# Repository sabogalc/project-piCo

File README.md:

# project piCo

This repository contains KiCad project files for reverse-engineered Raspberry Pi Pico boards, including both the standard RP2040 Pico H and the WiFi version, the Pico WH. There is also a preliminary design for an RP2350 Pico 2 board. The primary goal of this project is two-fold:

1. USB-C Upgrade: Although all Pico boards were released in or after 2021, they all use Micro-USB. The initial aim was to update these boards to include USB-C, making them more compatible with modern standards.

2. Accessibility of Design Files: During this process, I discovered that the original board designs are created in Cadence Allegro, a format that is less accessible due to its encrypted file structure and the expensive software required. This project not only adds USB-C support but also aims to make the design files as free and open as possible.

For detailed information on each board’s design, please refer to their specific folders within the `KiCad Projects` directory. Boardview files for all boards, including the original Pico H, are provided to allow for easy troubleshooting. The designs in this repository are freely available for use without any license restrictions or attribution requirements.

> The USB-C version of the Pico H board.

> The USB-C version of the Pico WH board.

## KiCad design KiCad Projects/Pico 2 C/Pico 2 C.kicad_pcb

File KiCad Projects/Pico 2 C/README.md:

# project piCo 2

I was extremely excited to see the announcement of the Pico 2 last week, but some of my enthusiasm left me when I saw that the new board still retained the Micro-USB connector. Of course, I got right to work on correcting this issue.

### Design Sources

Despite the online documentation and datasheet linking to design files for the board, the link appears to be broken as of August 14, 2024. (See [this issue](https://github.com/raspberrypi/documentation/issues/3809) for more information)

Still, I worked with the schematic and pictures of the board to be able to create an initial version of a Type-C Pico 2.

- **Schematic:** [Raspberry Pi Pico 2 Datasheet](https://datasheets.raspberrypi.com/pico/pico-2-datasheet.pdf#page=23)
- **PCB Pictures (Front & Back):** [Pico 2 PCB Photos](https://blog.zonepi.cz/rapsberry-pi-pico-2/)

Thankfully, with all the work I've already done on reversing the Pico, making this board was a breeze as I was able to reuse many of my assets and resources from the previous boards.

### Design Process

Kicad allows for Reference Images to be placed while routing a board (found in `Place > Add Reference Image`), so I put the aforementioned scans into the project to scale, and based my routing on the photo. This means that my board is not fully 1:1 with the factory one, but in lieu of the official design files, this was the best that could be done right now. An example of this layout is shown below.

### Component Substitutions (IMPORTANT)

As-is, this board is not ready for production. I was unable to figure out what component or footprint L2 is, other than that it is a coupled inductor and measures roughly 1.75x2.2mm. As a stand-in, I have placed an 0602 SMD inductor, but please note that this is **_not correct_**. As before, the boot select switch and 12MHz crystals are compatible substitutes (even though they told us what crystal was used this time, I just reused the asset I already had from the previous design).

### PDF Schematic

A PDF copy of the schematic is available [here](https://github.com/sabogalc/project-piCo/blob/main/KiCad%20Projects/Pico%202%20C/Pico%202%20C.pdf).

### Board Photos

Because of the aforementioned inductor issue, the only photos of this board right now are the KiCad renders. If anybody figures out what inductor this is, please either let me know or make a correction in the form of a pull request.

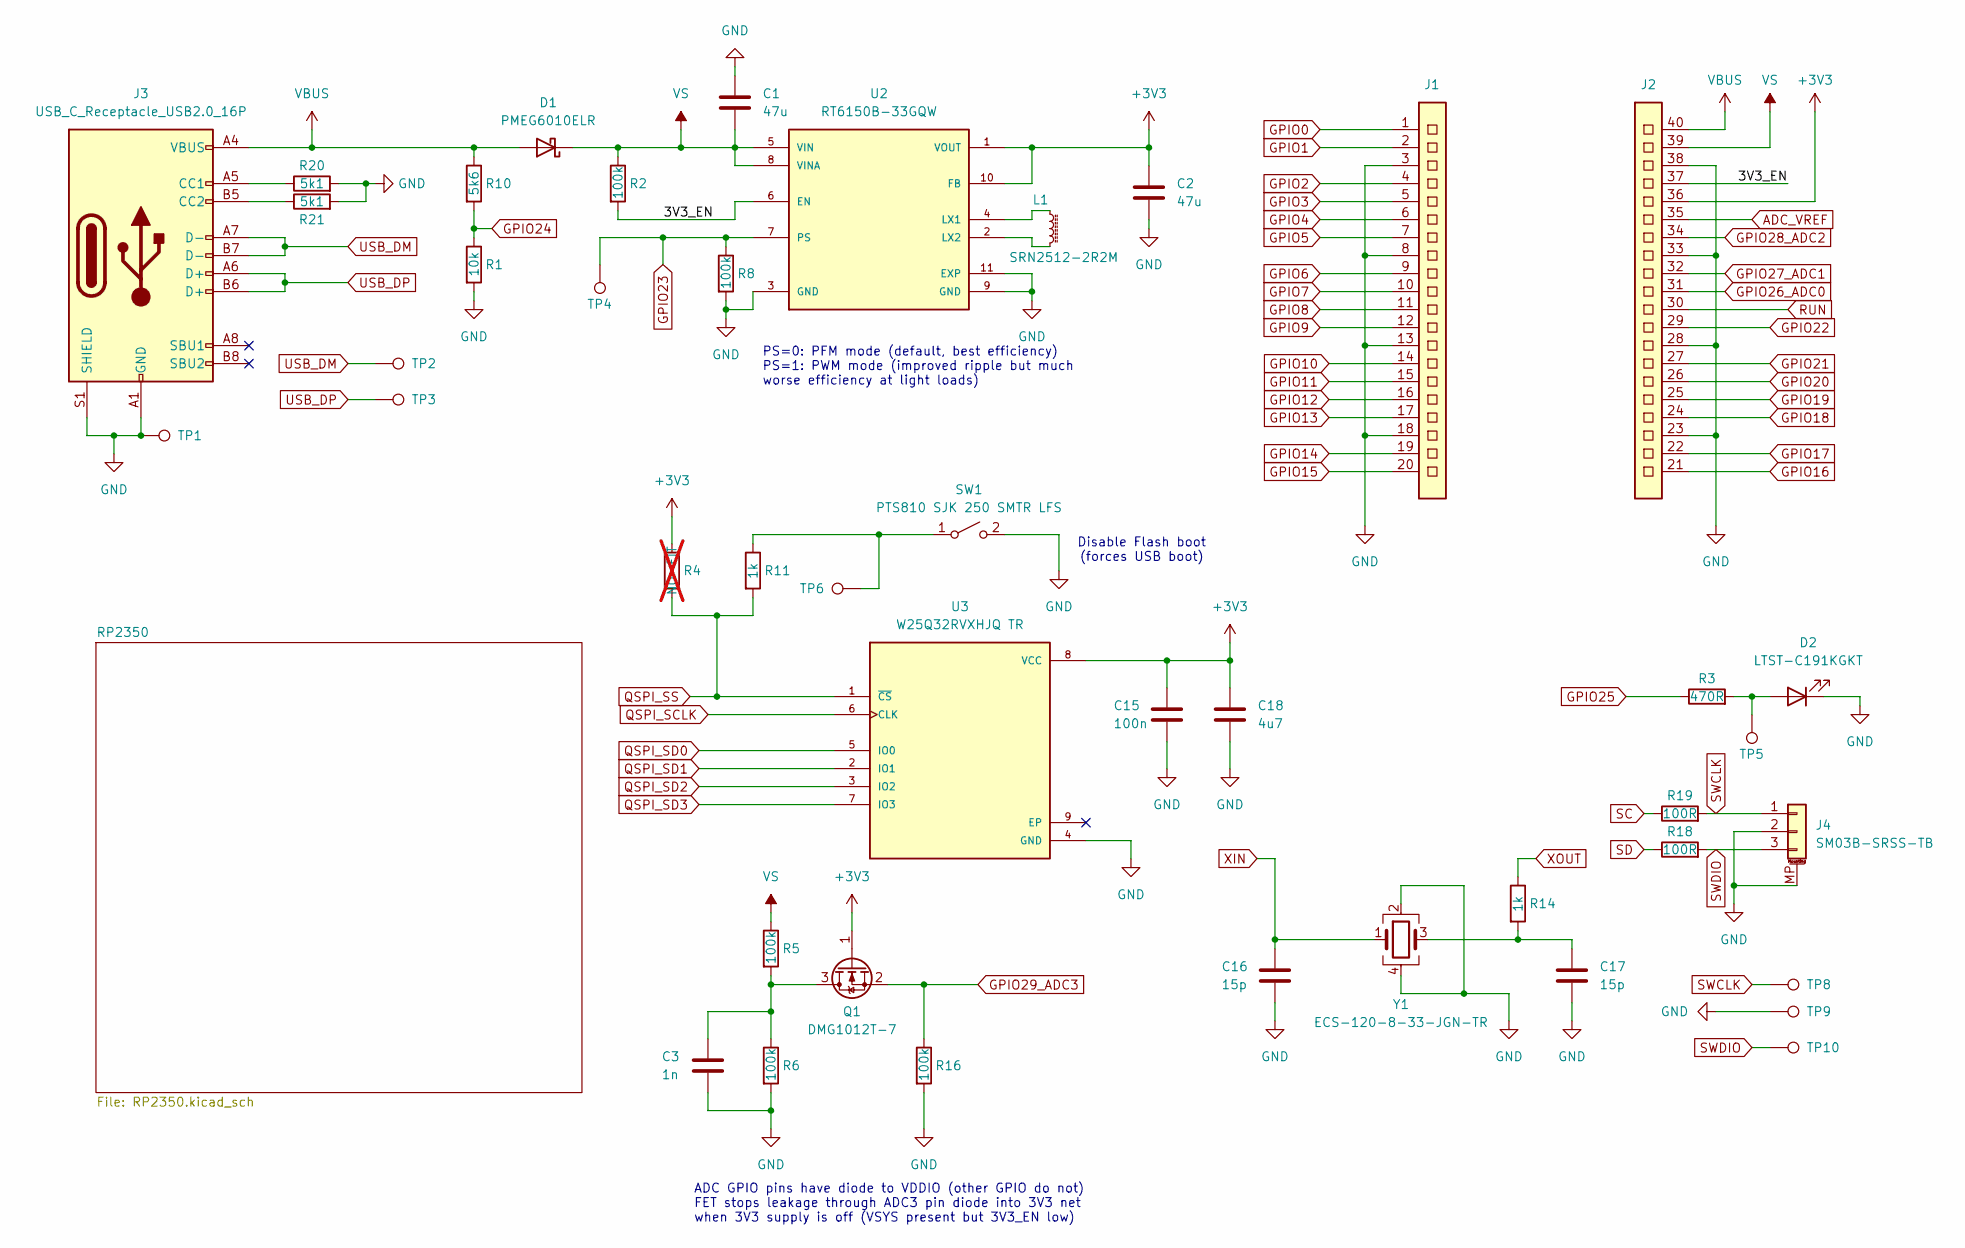
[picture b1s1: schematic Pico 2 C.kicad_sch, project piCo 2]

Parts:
C1, C2: 47u; C_0805_2012Metric
C3: 1n; C_0201_0603Metric
C15: 100n; C_0201_0603Metric
C16, C17: 15p; C_0201_0603Metric
C18: 4u7; C_0402_1005Metric
D1: PMEG6010ELR; D_SOD-123F
D2: LTST-C191KGKT; LED_0603_1608Metric
J1: CON_PICO_1-20
J2: CON_PICO_21-40
J3: USB_C_Receptacle_USB2.0_16P; USB_C_Receptacle_GCT_USB4105-xx-A_16P_TopMnt_Horizontal
J4: SM03B-SRSS-TB; JST_SH_SM03B-SRSS-TB_1x03-1MP_P1.00mm_Horizontal
L1: SRN2512-2R2M; L_1008_2520Metric
Q1: DMG1012T-7; SOT-523
R1: 10k; R_0201_0603Metric
R2, R5, R6, R8, R16: 100k; R_0201_0603Metric
R3: 470R; R_0201_0603Metric
R4: NO-FIT; R_0201_0603Metric; not fitted
R10: 5k6; R_0201_0603Metric
R11, R14: 1k; R_0201_0603Metric
R18, R19: 100R; R_0201_0603Metric
R20, R21: 5k1; R_0402_1005Metric
SW1: PTS810 SJK 250 SMTR LFS; SW_SPST_PTS810
TP1, TP2, TP3, TP4, TP5, TP6, TP8, TP9, TP10: TestPoint; TestPoint_Pad_1.5x1.5mm
U2: RT6150B-33GQW; DFN-10-1EP_2.6x2.6mm_P0.5mm_EP1.3x2.2mm
U3: W25Q32RVXHJQ TR; TDFN-8-1EP_3x2mm_P0.5mm_EP1.3x1.4mm
Y1: ECS-120-8-33-JGN-TR; Crystal_SMD_SeikoEpson_FA238-4Pin_3.2x2.5mm

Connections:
+3V3: C2.1, C15.1, C18.1, J2.36, Q1.1 (G), R4.1, U2.1 (VOUT), U2.10 (FB), U3.8 (VCC); also elsewhere on the board
/3V3_EN: J2.37, R2.2, U2.6 (EN)
ADC_VREF: J2.35; also elsewhere on the board
GND: C1.2, C2.2, C3.2, C15.2, C16.2, C17.2, C18.2, D2.1 (K), J1.3, J1.8, J1.13, J1.18, J2.23, J2.28, J2.33, J2.38, J3.A1 (GND), J3.A12 (GND), J3.B1 (GND), J3.B12 (GND), J3.S1 (SHIELD), J4.2, J4.MP (MountPin), R1.2, R6.2, R8.2, R16.2, R20.2, R21.2, SW1.2 (B), TP1.1, TP9.1, U2.3 (GND), U2.9 (GND), U2.11 (EXP), U3.4 (GND), Y1.2, Y1.4; also elsewhere on the board
GPIO0: J1.1; also elsewhere on the board
GPIO1: J1.2; also elsewhere on the board
GPIO2: J1.4; also elsewhere on the board
GPIO3: J1.5; also elsewhere on the board
GPIO4: J1.6; also elsewhere on the board
GPIO5: J1.7; also elsewhere on the board
GPIO6: J1.9; also elsewhere on the board
GPIO7: J1.10; also elsewhere on the board
GPIO8: J1.11; also elsewhere on the board
GPIO9: J1.12; also elsewhere on the board
GPIO10: J1.14; also elsewhere on the board
GPIO11: J1.15; also elsewhere on the board
GPIO12: J1.16; also elsewhere on the board
GPIO13: J1.17; also elsewhere on the board
GPIO14: J1.19; also elsewhere on the board
GPIO15: J1.20; also elsewhere on the board
GPIO16: J2.21; also elsewhere on the board
GPIO17: J2.22; also elsewhere on the board
GPIO18: J2.24; also elsewhere on the board
GPIO19: J2.25; also elsewhere on the board
GPIO20: J2.26; also elsewhere on the board
GPIO21: J2.27; also elsewhere on the board
GPIO22: J2.29; also elsewhere on the board
GPIO23: R8.1, TP4.1, U2.7 (PS); also elsewhere on the board
GPIO24: R1.1, R10.2; also elsewhere on the board
GPIO25: R3.1; also elsewhere on the board
GPIO26_ADC0: J2.31; also elsewhere on the board
GPIO27_ADC1: J2.32; also elsewhere on the board
GPIO28_ADC2: J2.34; also elsewhere on the board
GPIO29_ADC3: Q1.2 (S), R16.1; also elsewhere on the board
unnamed: C17.1, R14.2, Y1.3
unnamed: D2.2 (A), R3.2, TP5.1
unnamed: J3.A5 (CC1), R20.1
unnamed: J3.B5 (CC2), R21.1
unnamed: C3.1, Q1.3 (D), R5.2, R6.1
unnamed: R11.1, SW1.1 (A), TP6.1
unnamed: L1.1, U2.4 (LX1)
unnamed: L1.2, U2.2 (LX2)
QSPI_SCLK: U3.6 (CLK); also elsewhere on the board
QSPI_SD0: U3.5 (IO0); also elsewhere on the board
QSPI_SD1: U3.2 (IO1); also elsewhere on the board
QSPI_SD2: U3.3 (IO2); also elsewhere on the board
QSPI_SD3: U3.7 (IO3); also elsewhere on the board
QSPI_SS: R4.2, R11.2, U3.1 (~CS); also elsewhere on the board
RUN: J2.30; also elsewhere on the board
SC: R19.1; also elsewhere on the board
SD: R18.1; also elsewhere on the board
SWCLK: J4.1, R19.2, TP8.1
SWDIO: J4.3, R18.2, TP10.1
USB_DM: J3.A7 (D-), J3.B7 (D-), TP2.1; also elsewhere on the board
USB_DP: J3.A6 (D+), J3.B6 (D+), TP3.1; also elsewhere on the board
VBUS: D1.2 (A), J2.40, J3.A4 (VBUS), J3.A9 (VBUS), J3.B4 (VBUS), J3.B9 (VBUS), R10.1
VS: C1.1, D1.1 (K), J2.39, R2.1, R5.1, U2.5 (VIN), U2.8 (VINA)
XIN: C16.1, Y1.1; also elsewhere on the board
XOUT: R14.1; also elsewhere on the board

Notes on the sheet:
ADC GPIO pins have diode to VDDIO (other GPIO do not) FET stops leakage through ADC3 pin diode into 3V3 net when 3V3 supply is off (VSYS present but 3V3_EN low)
Disable Flash boot (forces USB boot)
PS=0: PFM mode (default, best efficiency) PS=1: PWM mode (improved ripple but much worse efficiency at light loads)

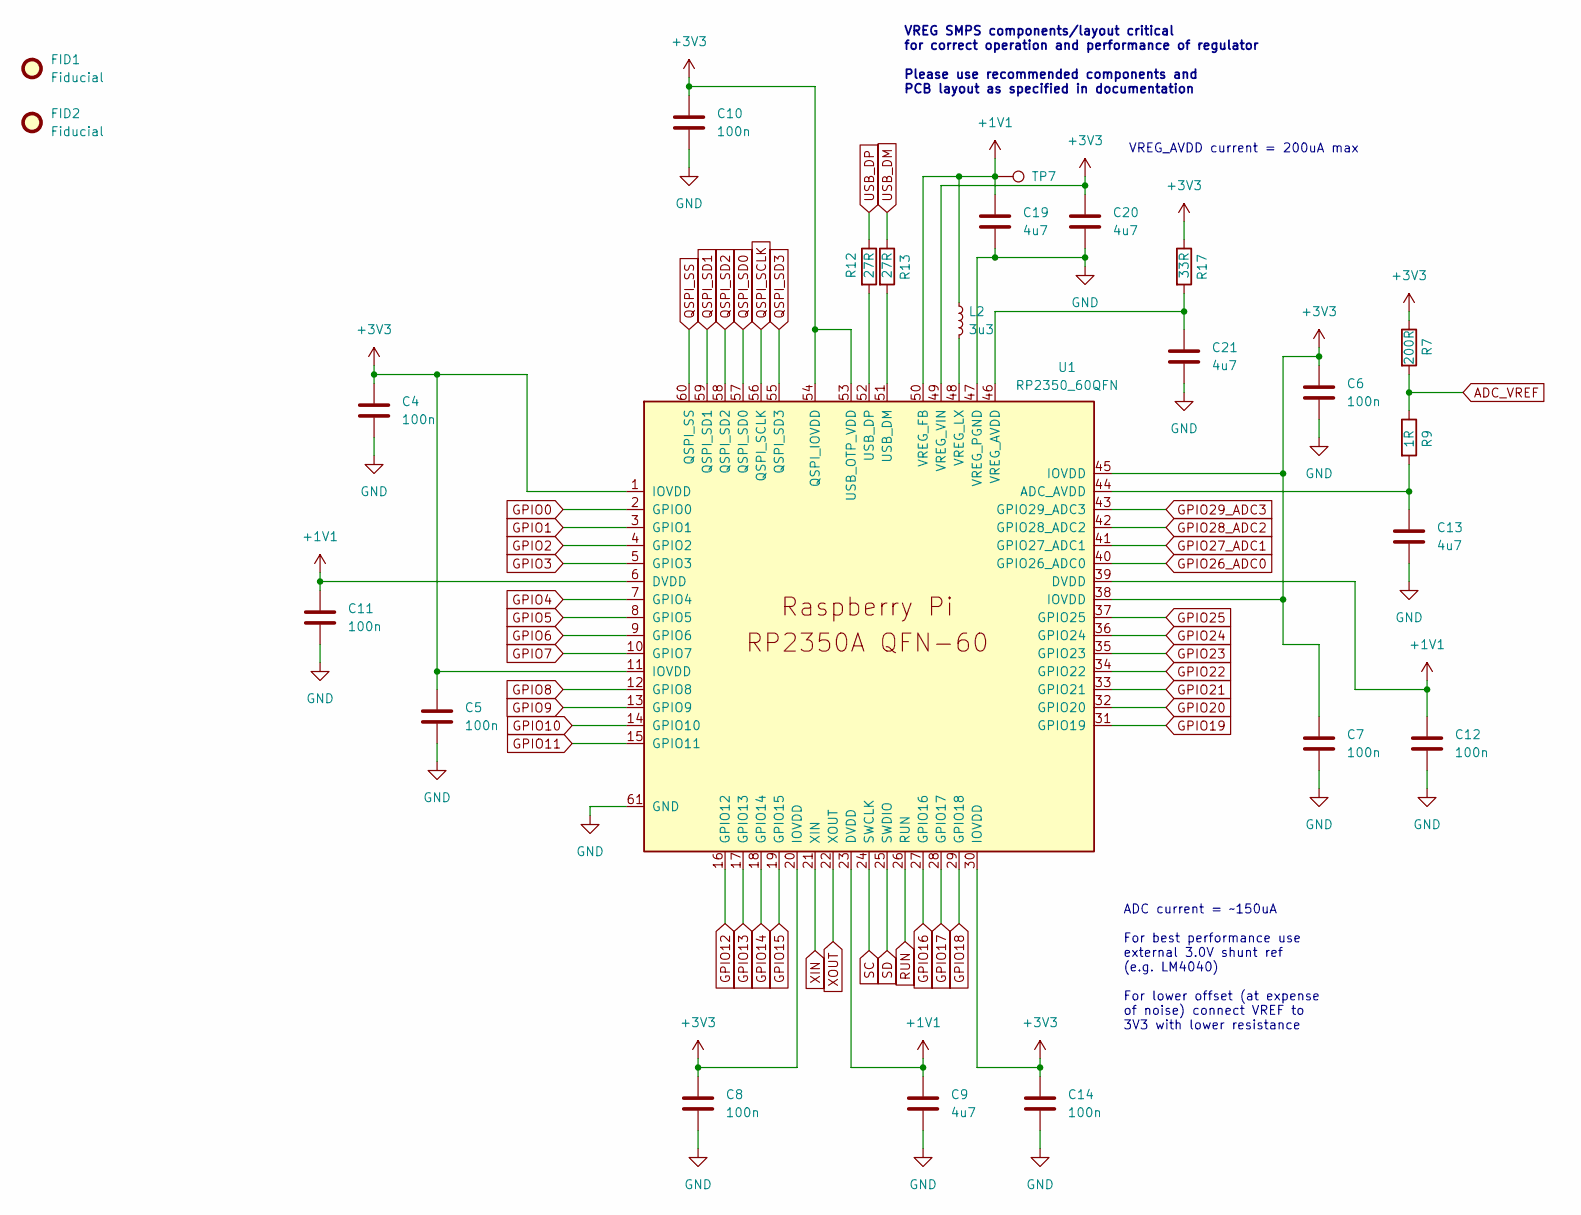
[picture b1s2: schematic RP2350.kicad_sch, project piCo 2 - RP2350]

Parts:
C4, C5, C6, C7, C8, C10, C11, C12, C14: 100n; C_0201_0603Metric
C9: 4u7; C_0201_0603Metric
C13, C19, C20, C21: 4u7; C_0402_1005Metric
FID1, FID2: Fiducial; Fiducial_1mm_Mask2mm
L2: 3u3; AOTA-B201610S3R3-101-T
R7: 200R; R_0402_1005Metric
R9: 1R; R_0201_0603Metric
R12, R13: 27R; R_0201_0603Metric
R17: 33R; R_0402_1005Metric
TP7: TestPoint; TestPoint_Pad_1.5x1.5mm
U1: RP2350_60QFN; RP2350-QFN-60-1EP_7x7_P0.4mm_EP3.4x3.4mm_ThermalVias

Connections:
+1V1: C9.1, C11.1, C12.1, C19.1, L2.1, TP7.1, U1.6 (DVDD), U1.23 (DVDD), U1.39 (DVDD), U1.50 (VREG_FB)
+3V3: C4.1, C5.1, C6.1, C7.1, C8.1, C10.1, C14.1, C20.1, R7.1, R17.1, U1.1 (IOVDD), U1.11 (IOVDD), U1.20 (IOVDD), U1.30 (IOVDD), U1.38 (IOVDD), U1.45 (IOVDD), U1.49 (VREG_VIN), U1.53 (USB_OTP_VDD), U1.54 (QSPI_IOVDD); also elsewhere on the board
ADC_VREF: R7.2, R9.1; also elsewhere on the board
GND: C4.2, C5.2, C6.2, C7.2, C8.2, C9.2, C10.2, C11.2, C12.2, C13.2, C14.2, C19.2, C20.2, C21.2, U1.47 (VREG_PGND), U1.61 (GND); also elsewhere on the board
GPIO0: U1.2 (GPIO0); also elsewhere on the board
GPIO1: U1.3 (GPIO1); also elsewhere on the board
GPIO2: U1.4 (GPIO2); also elsewhere on the board
GPIO3: U1.5 (GPIO3); also elsewhere on the board
GPIO4: U1.7 (GPIO4); also elsewhere on the board
GPIO5: U1.8 (GPIO5); also elsewhere on the board
GPIO6: U1.9 (GPIO6); also elsewhere on the board
GPIO7: U1.10 (GPIO7); also elsewhere on the board
GPIO8: U1.12 (GPIO8); also elsewhere on the board
GPIO9: U1.13 (GPIO9); also elsewhere on the board
GPIO10: U1.14 (GPIO10); also elsewhere on the board
GPIO11: U1.15 (GPIO11); also elsewhere on the board
GPIO12: U1.16 (GPIO12); also elsewhere on the board
GPIO13: U1.17 (GPIO13); also elsewhere on the board
GPIO14: U1.18 (GPIO14); also elsewhere on the board
GPIO15: U1.19 (GPIO15); also elsewhere on the board
GPIO16: U1.27 (GPIO16); also elsewhere on the board
GPIO17: U1.28 (GPIO17); also elsewhere on the board
GPIO18: U1.29 (GPIO18); also elsewhere on the board
GPIO19: U1.31 (GPIO19); also elsewhere on the board
GPIO20: U1.32 (GPIO20); also elsewhere on the board
GPIO21: U1.33 (GPIO21); also elsewhere on the board
GPIO22: U1.34 (GPIO22); also elsewhere on the board
GPIO23: U1.35 (GPIO23); also elsewhere on the board
GPIO24: U1.36 (GPIO24); also elsewhere on the board
GPIO25: U1.37 (GPIO25); also elsewhere on the board
GPIO26_ADC0: U1.40 (GPIO26_ADC0); also elsewhere on the board
GPIO27_ADC1: U1.41 (GPIO27_ADC1); also elsewhere on the board
GPIO28_ADC2: U1.42 (GPIO28_ADC2); also elsewhere on the board
GPIO29_ADC3: U1.43 (GPIO29_ADC3); also elsewhere on the board
unnamed: C13.1, R9.2, U1.44 (ADC_AVDD)
unnamed: R13.2, U1.51 (USB_DM)
unnamed: R12.2, U1.52 (USB_DP)
unnamed: C21.1, R17.2, U1.46 (VREG_AVDD)
unnamed: L2.2, U1.48 (VREG_LX)
QSPI_SCLK: U1.56 (QSPI_SCLK); also elsewhere on the board
QSPI_SD0: U1.57 (QSPI_SD0); also elsewhere on the board
QSPI_SD1: U1.59 (QSPI_SD1); also elsewhere on the board
QSPI_SD2: U1.58 (QSPI_SD2); also elsewhere on the board
QSPI_SD3: U1.55 (QSPI_SD3); also elsewhere on the board
QSPI_SS: U1.60 (QSPI_SS); also elsewhere on the board
RUN: U1.26 (RUN); also elsewhere on the board
SC: U1.24 (SWCLK); also elsewhere on the board
SD: U1.25 (SWDIO); also elsewhere on the board
USB_DM: R13.1; also elsewhere on the board
USB_DP: R12.1; also elsewhere on the board
XIN: U1.21 (XIN); also elsewhere on the board
XOUT: U1.22 (XOUT); also elsewhere on the board

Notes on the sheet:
VREG SMPS components/layout critical for correct operation and performance of regulator Please use recommended components and PCB layout as specified in documentation
ADC current = ~150uA For best performance use external 3.0V shunt ref (e.g. LM4040) For lower offset (at expense of noise) connect VREF to 3V3 with lower resistance
VREG_AVDD current = 200uA max

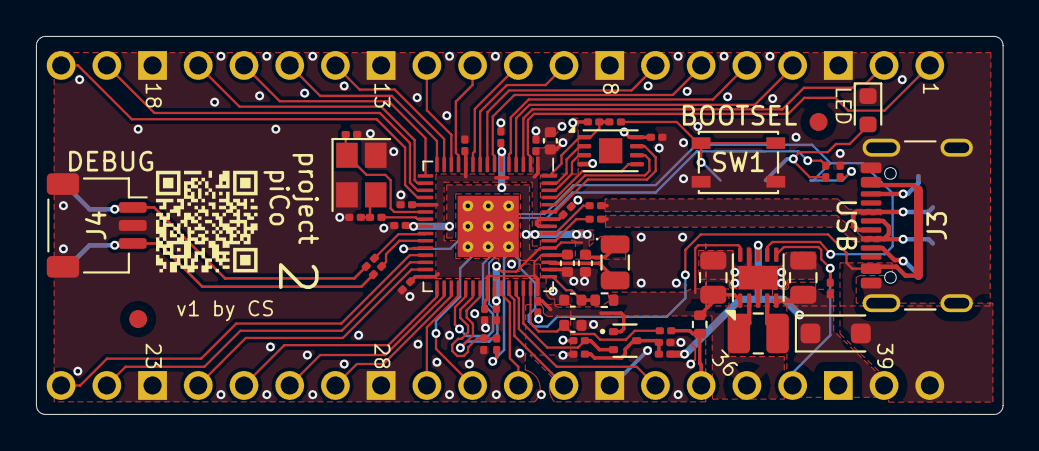
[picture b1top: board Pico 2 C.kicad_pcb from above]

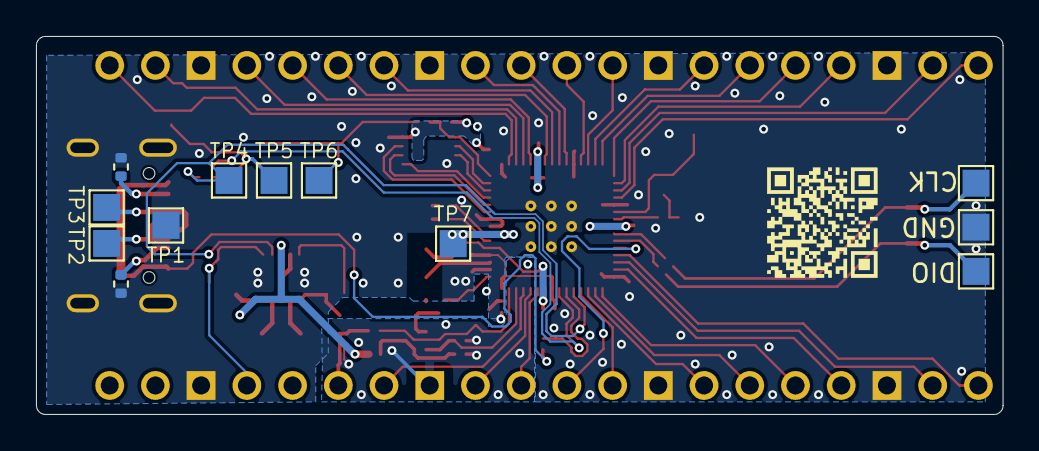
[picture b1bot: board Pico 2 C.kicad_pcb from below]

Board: 2 copper layers, 53.7 x 21.0 mm, 67 parts (12 on the bottom side), 65 nets.

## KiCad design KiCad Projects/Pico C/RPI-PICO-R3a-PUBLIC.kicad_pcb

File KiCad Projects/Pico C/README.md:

# project piCo

This is a completely reverse-engineered Raspberry Pi Pico H made in KiCad version 8. The Raspberry Pi Foundation offers schematics and board layout files for the original board, but they are made in Cadence Allegro, which costs a crisp $1,500/month that I do not have. Instead, I opted to recreate the board in KiCad so that I could add a Type-C port.

### Overview

Initially, I developed a PCB to convert the original Micro-USB signals to a Type-C breakout board. However, the tolerances were really tight, and it didn't look like much of a finished product. My boss gave me a suggestion to redesign the entire board and add a Type-C port to it, which is what I ended up doing. I started the process with the original design files, which you can find in the section below.

### Design Sources

- **Schematic:** [Raspberry Pi Pico Datasheet](https://datasheets.raspberrypi.com/pico/pico-datasheet.pdf#page=26)
- **PCB Design Files:** [RPi Pico R3 Files](https://datasheets.raspberrypi.com/pico/RPi-Pico-R3-PUBLIC-20200119.zip) (Note: This link will download files directly.)
- **BOM:** [Pico Bill of Materials](https://archive.is/NHUY5)

The mechanical layout provided by the Pi Foundation was extremely useful in creating my board dimensions. Since my footprint was made in KiCad, anybody should be able to implement it for their own projects.

### Footprint Differences

The project includes a footprint named "CON_PICO_40W," which replicates the original footprint, and a modified version, "CON_PICO_40W_VER_C," which is used in my design. Key differences are highlighted below.

### Design Evolution

Version 1 of the board had many issues. You can see that version [here](https://github.com/sabogalc/project-piCo/tree/4ffbc08c13815f0195cdc85224667cf2c5e13563). The biggest challenge was fitting the Type-C port within the original dimensions.

When I published this project, many people let me know that Type-C Pico clones already exist, so I modeled my redesign after the purple clone board from [this AliExpress listing](https://www.aliexpress.com/item/3256805444428998.html).

The revised design removed the 4 mounting holes and added space for the Type-C port, which vastly improved my ability to design and route this board. The "CON_PICO_40W_VER_C" footprint used in this revision is a copy of the purple clone board. Sometimes you just need to [reverse-engineer the reverse-engineers](https://youtu.be/FVEQJNRmfDQ?t=431).

### Component Substitutions

I could not find the original boot select switch, Schottky diode, or 12MHz crystal in stock anywhere, but the substitutions I made should be plug-and-play.

### PDF Schematic

For those of you without KiCad or that just want to take a quick look at the schematic, a [PDF version](https://github.com/sabogalc/project-piCo/blob/main/KiCad%20Projects/Pico%20C/RPI-PICO-R3a-PUBLIC.pdf) is available.

### Version 4 - A 1:1 recreation

[Version 3](https://github.com/sabogalc/project-piCo/tree/0116e01858a51d29eb83f16cde15d637a825e509) of this board improved on [version 2](https://github.com/sabogalc/project-piCo/tree/e2333728981e60bb3f34c05a658cf739d1d45163) in regards to copper pours, routing, and silkscreen labeling. However, versions 1-3 were all routed from scratch by myself. As seen below in the `Official Files` section or in the [piCo W folder](https://github.com/sabogalc/project-piCo/tree/main/KiCad%20Projects/Pico%20WH%20-%20No%20License), I later learned how to convert a Cadence Allegro board into a KiCad one, and this allows me to make a 1:1 PCB when reverse-engineering. Version 4 is this 1:1 render, and it should theoretically be the last version of this board.

When it comes to improving the Pico, I have thought about making design improvements to the ADC or adding a reset switch. However, the overall purpose of this project is to be 1:1 with the layout and parts of an original Pico, though if anyone finds any room for improvement I would be happy to make any fixes (e.g. the grid on the schematic is not standard and could use correction).

_**DISCLAIMER**_

I have interned at this company for almost two years.

For those of you that want a board with the aforementioned improvements, check out the [RP2040 board from Out of the Box](https://www.ootbelec.com/store/p/ootb-rp2040).

### Official Files

I have updated this folder to include a file called `RPI-PICO-R3a-PUBLIC - Official.kicad_pcb`. This is as close to the original Cadence Allegro design file that I could get imported into KiCad. I first converted the Allegro board into an Altium one, and then I converted the Altium board into KiCad.

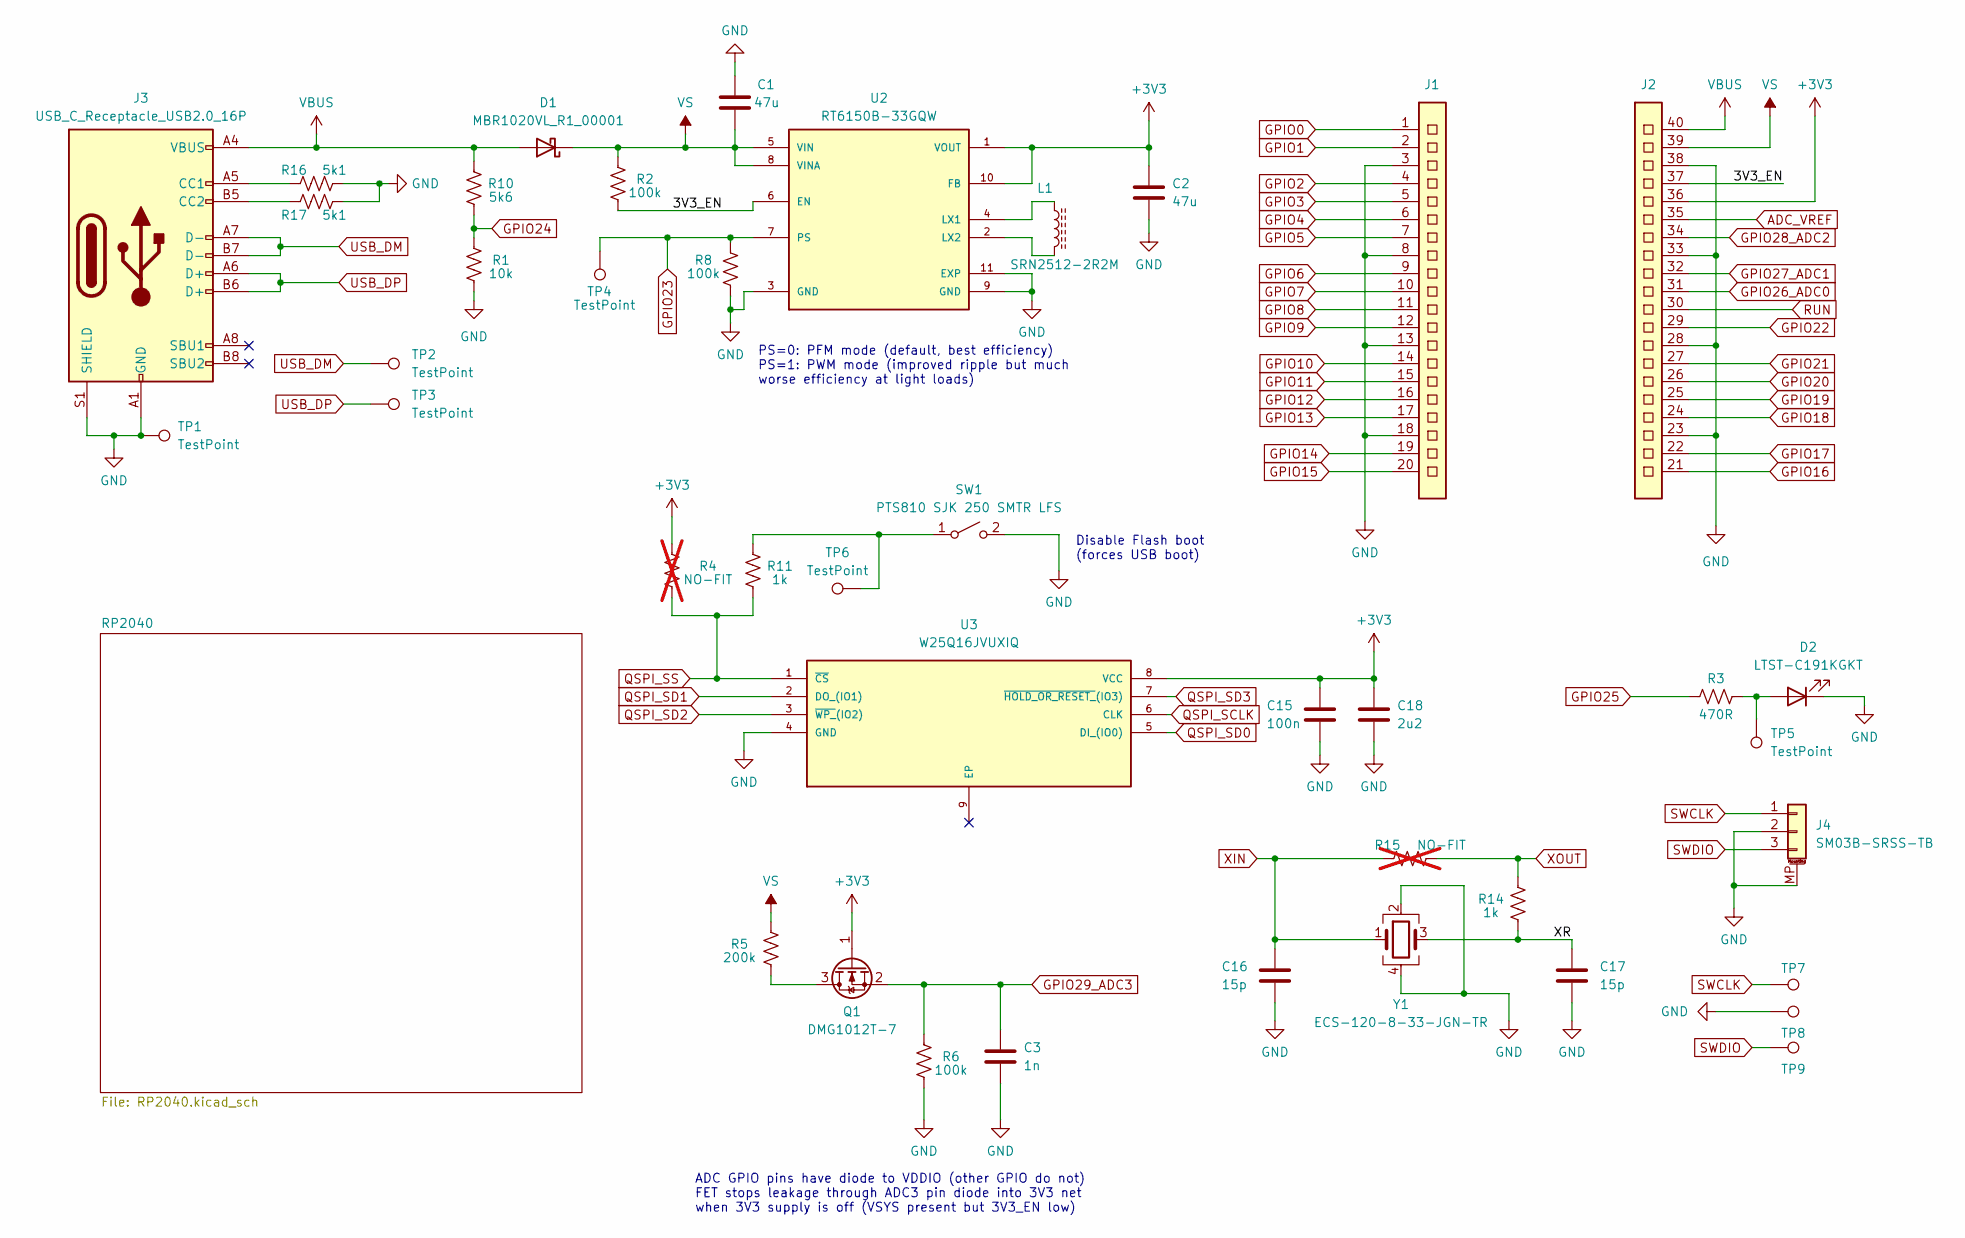
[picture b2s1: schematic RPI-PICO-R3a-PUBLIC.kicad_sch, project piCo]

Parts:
C1, C2: 47u; C_0805_2012Metric
C3: 1n; C_0201_0603Metric
C15: 100n; C_0201_0603Metric
C16, C17: 15p; C_0201_0603Metric
C18: 2u2; C_0402_1005Metric
D1: MBR1020VL_R1_00001; D_SOD-123F
D2: LTST-C191KGKT; LED_0603_1608Metric
J1: CON_PICO_1-20
J2: CON_PICO_21-40
J3: USB_C_Receptacle_USB2.0_16P; USB_C_Receptacle_GCT_USB4105-xx-A_16P_TopMnt_Horizontal
J4: SM03B-SRSS-TB; JST_SH_SM03B-SRSS-TB_1x03-1MP_P1.00mm_Horizontal
L1: SRN2512-2R2M; L_1008_2520Metric
Q1: DMG1012T-7; SOT-523
R1: 10k; R_0402_1005Metric
R2, R6, R8: 100k; R_0402_1005Metric
R3: 470R; R_0402_1005Metric
R4, R15: NO-FIT; R_0402_1005Metric; not fitted
R5: 200k; R_0402_1005Metric
R10: 5k6; R_0402_1005Metric
R11, R14: 1k; R_0402_1005Metric
R16, R17: 5k1; R_0402_1005Metric
SW1: PTS810 SJK 250 SMTR LFS; SW_SPST_PTS810
TP1, TP2, TP3, TP4, TP5, TP6, TP7, TP8, TP9: TestPoint; TestPoint_Pad_1.5x1.5mm
U2: RT6150B-33GQW; DFN-10-1EP_2.6x2.6mm_P0.5mm_EP1.3x2.2mm
U3: W25Q16JVUXIQ; SON50P300X200X60-9N
Y1: ECS-120-8-33-JGN-TR; Crystal_SMD_SeikoEpson_FA238-4Pin_3.2x2.5mm

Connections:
+3V3: C2.1, C15.1, C18.1, J2.36, Q1.1 (G), R4.2, U2.1 (VOUT), U2.10 (FB), U3.8 (VCC); also elsewhere on the board
/3V3_EN: J2.37, R2.1, U2.6 (EN)
/XR: C17.1, R14.1, Y1.3
ADC_VREF: J2.35; also elsewhere on the board
GND: C1.2, C2.2, C3.2, C15.2, C16.2, C17.2, C18.2, D2.1 (K), J1.3, J1.8, J1.13, J1.18, J2.23, J2.28, J2.33, J2.38, J3.A1 (GND), J3.A12 (GND), J3.B1 (GND), J3.B12 (GND), J3.S1 (SHIELD), J4.2, J4.MP (MountPin), R1.1, R6.1, R8.2, R16.2, R17.2, SW1.2 (B), TP1.1, TP8.1, U2.3 (GND), U2.9 (GND), U2.11 (EXP), U3.4 (GND), Y1.2, Y1.4; also elsewhere on the board
GPIO0: J1.1; also elsewhere on the board
GPIO1: J1.2; also elsewhere on the board
GPIO2: J1.4; also elsewhere on the board
GPIO3: J1.5; also elsewhere on the board
GPIO4: J1.6; also elsewhere on the board
GPIO5: J1.7; also elsewhere on the board
GPIO6: J1.9; also elsewhere on the board
GPIO7: J1.10; also elsewhere on the board
GPIO8: J1.11; also elsewhere on the board
GPIO9: J1.12; also elsewhere on the board
GPIO10: J1.14; also elsewhere on the board
GPIO11: J1.15; also elsewhere on the board
GPIO12: J1.16; also elsewhere on the board
GPIO13: J1.17; also elsewhere on the board
GPIO14: J1.19; also elsewhere on the board
GPIO15: J1.20; also elsewhere on the board
GPIO16: J2.21; also elsewhere on the board
GPIO17: J2.22; also elsewhere on the board
GPIO18: J2.24; also elsewhere on the board
GPIO19: J2.25; also elsewhere on the board
GPIO20: J2.26; also elsewhere on the board
GPIO21: J2.27; also elsewhere on the board
GPIO22: J2.29; also elsewhere on the board
GPIO23: R8.1, TP4.1, U2.7 (PS); also elsewhere on the board
GPIO24: R1.2, R10.1; also elsewhere on the board
GPIO25: R3.1; also elsewhere on the board
GPIO26_ADC0: J2.31; also elsewhere on the board
GPIO27_ADC1: J2.32; also elsewhere on the board
GPIO28_ADC2: J2.34; also elsewhere on the board
GPIO29_ADC3: C3.1, Q1.2 (S), R6.2; also elsewhere on the board
unnamed: D2.2 (A), R3.2, TP5.1
unnamed: J3.A5 (CC1), R16.1
unnamed: J3.B5 (CC2), R17.1
unnamed: Q1.3 (D), R5.1
unnamed: R11.2, SW1.1 (A), TP6.1
unnamed: L1.1, U2.4 (LX1)
unnamed: L1.2, U2.2 (LX2)
QSPI_SCLK: U3.6 (CLK); also elsewhere on the board
QSPI_SD0: U3.5 (DI_(IO0)); also elsewhere on the board
QSPI_SD1: U3.2 (DO_(IO1)); also elsewhere on the board
QSPI_SD2: U3.3 (~WP_(IO2)); also elsewhere on the board
QSPI_SD3: U3.7 (~HOLD_OR_RESET_(IO3)); also elsewhere on the board
QSPI_SS: R4.1, R11.1, U3.1 (~CS); also elsewhere on the board
RUN: J2.30; also elsewhere on the board
SWCLK: J4.1, TP7.1; also elsewhere on the board
SWDIO: J4.3, TP9.1; also elsewhere on the board
USB_DM: J3.A7 (D-), J3.B7 (D-), TP2.1; also elsewhere on the board
USB_DP: J3.A6 (D+), J3.B6 (D+), TP3.1; also elsewhere on the board
VBUS: D1.2 (A), J2.40, J3.A4 (VBUS), J3.A9 (VBUS), J3.B4 (VBUS), J3.B9 (VBUS), R10.2
VS: C1.1, D1.1 (K), J2.39, R2.2, R5.2, U2.5 (VIN), U2.8 (VINA)
XIN: C16.1, R15.1, Y1.1; also elsewhere on the board
XOUT: R14.2, R15.2; also elsewhere on the board

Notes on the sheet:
PS=0: PFM mode (default, best efficiency) PS=1: PWM mode (improved ripple but much worse efficiency at light loads)
ADC GPIO pins have diode to VDDIO (other GPIO do not) FET stops leakage through ADC3 pin diode into 3V3 net when 3V3 supply is off (VSYS present but 3V3_EN low)
Disable Flash boot (forces USB boot)

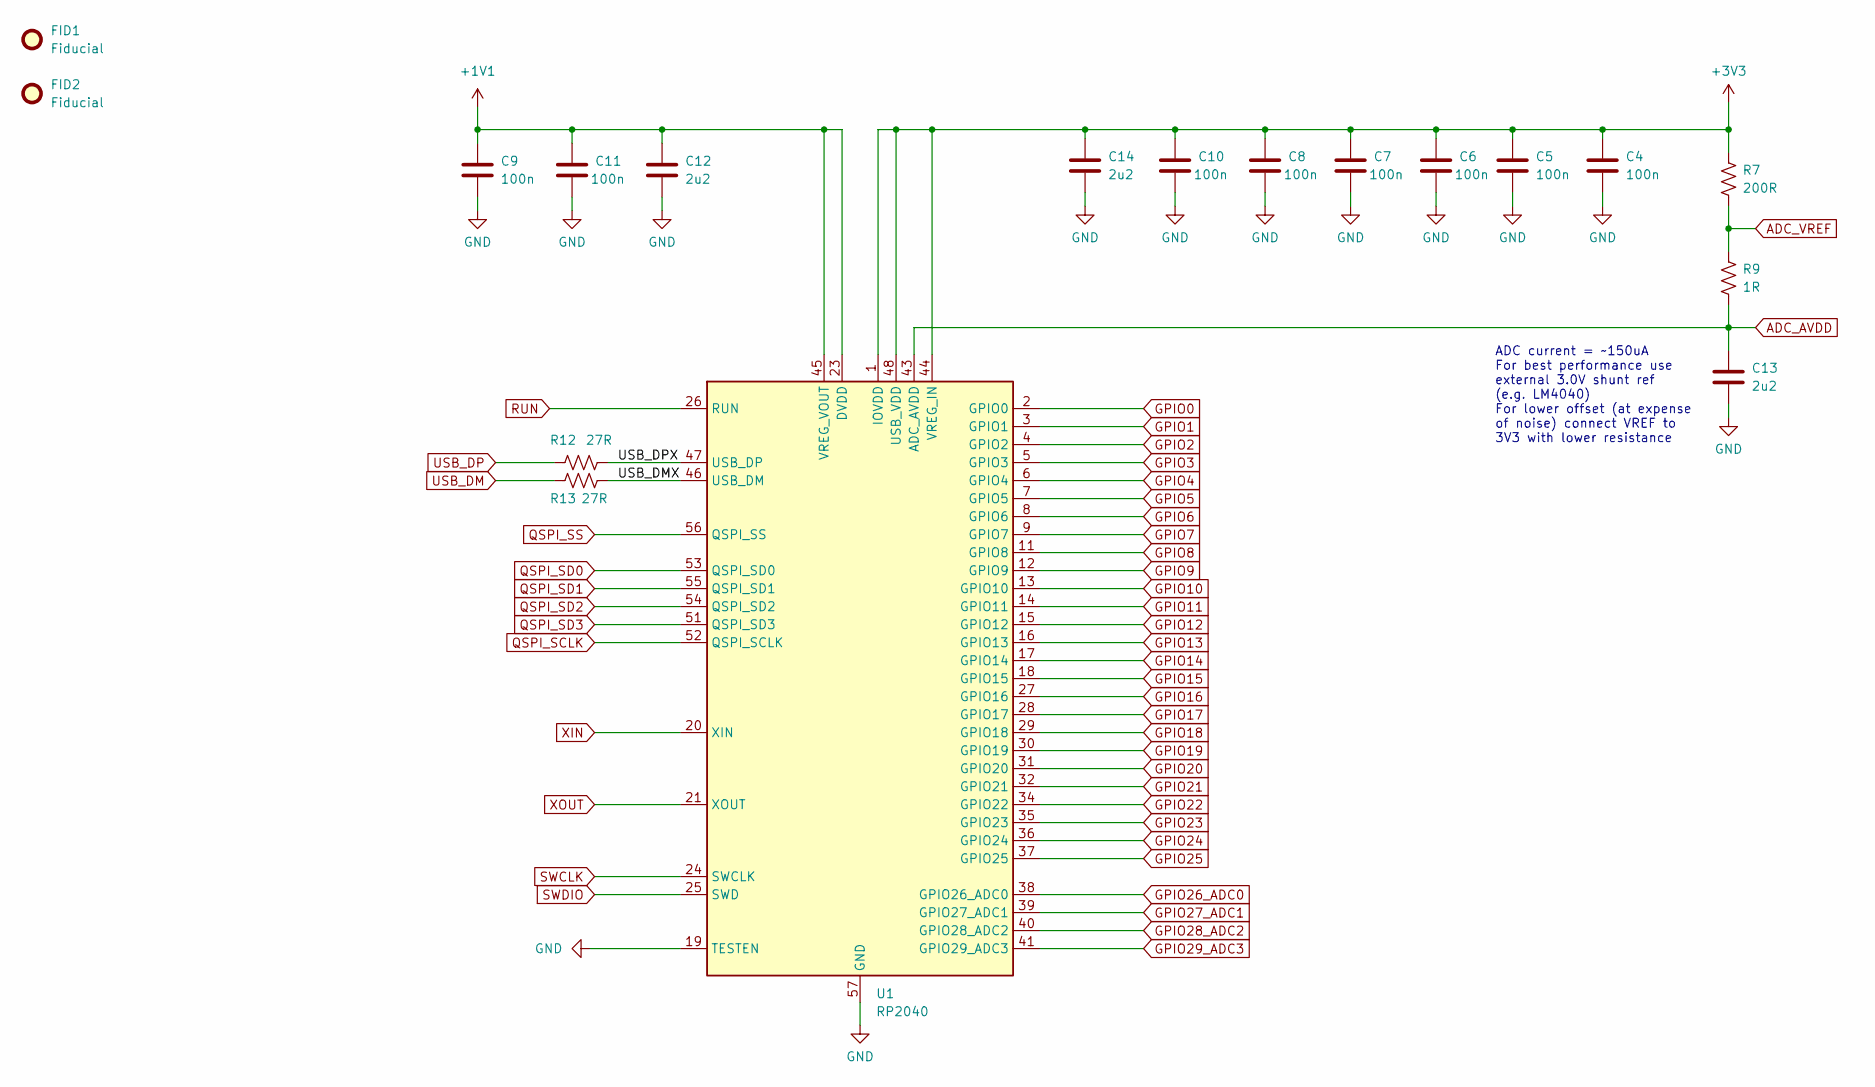
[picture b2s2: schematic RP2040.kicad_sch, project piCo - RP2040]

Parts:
C4, C5, C6, C7, C8, C9, C10, C11: 100n; C_0201_0603Metric
C12, C13, C14: 2u2; C_0402_1005Metric
FID1, FID2: Fiducial; Fiducial_1mm_Mask2mm
R7: 200R; R_0603_1608Metric
R9: 1R; R_0402_1005Metric
R12, R13: 27R; R_0201_0603Metric
U1: RP2040; QFN-56-1EP_7x7mm_P0.4mm_EP3.2x3.2mm

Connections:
+1V1: C9.1, C11.1, C12.1, U1.23 (DVDD), U1.45 (VREG_VOUT), U1.50 (DVDD)
+3V3: C4.1, C5.1, C6.1, C7.1, C8.1, C10.1, C14.1, R7.1, U1.1 (IOVDD), U1.10 (IOVDD), U1.22 (IOVDD), U1.33 (IOVDD), U1.42 (IOVDD), U1.44 (VREG_IN), U1.48 (USB_VDD), U1.49 (IOVDD); also elsewhere on the board
/RP2040/USB_DMX: R13.2, U1.46 (USB_DM)
/RP2040/USB_DPX: R12.2, U1.47 (USB_DP)
ADC_AVDD: C13.1, R9.2, U1.43 (ADC_AVDD)
ADC_VREF: R7.2, R9.1; also elsewhere on the board
GND: C4.2, C5.2, C6.2, C7.2, C8.2, C9.2, C10.2, C11.2, C12.2, C13.2, C14.2, U1.19 (TESTEN), U1.57 (GND); also elsewhere on the board
GPIO0: U1.2 (GPIO0); also elsewhere on the board
GPIO1: U1.3 (GPIO1); also elsewhere on the board
GPIO2: U1.4 (GPIO2); also elsewhere on the board
GPIO3: U1.5 (GPIO3); also elsewhere on the board
GPIO4: U1.6 (GPIO4); also elsewhere on the board
GPIO5: U1.7 (GPIO5); also elsewhere on the board
GPIO6: U1.8 (GPIO6); also elsewhere on the board
GPIO7: U1.9 (GPIO7); also elsewhere on the board
GPIO8: U1.11 (GPIO8); also elsewhere on the board
GPIO9: U1.12 (GPIO9); also elsewhere on the board
GPIO10: U1.13 (GPIO10); also elsewhere on the board
GPIO11: U1.14 (GPIO11); also elsewhere on the board
GPIO12: U1.15 (GPIO12); also elsewhere on the board
GPIO13: U1.16 (GPIO13); also elsewhere on the board
GPIO14: U1.17 (GPIO14); also elsewhere on the board
GPIO15: U1.18 (GPIO15); also elsewhere on the board
GPIO16: U1.27 (GPIO16); also elsewhere on the board
GPIO17: U1.28 (GPIO17); also elsewhere on the board
GPIO18: U1.29 (GPIO18); also elsewhere on the board
GPIO19: U1.30 (GPIO19); also elsewhere on the board
GPIO20: U1.31 (GPIO20); also elsewhere on the board
GPIO21: U1.32 (GPIO21); also elsewhere on the board
GPIO22: U1.34 (GPIO22); also elsewhere on the board
GPIO23: U1.35 (GPIO23); also elsewhere on the board
GPIO24: U1.36 (GPIO24); also elsewhere on the board
GPIO25: U1.37 (GPIO25); also elsewhere on the board
GPIO26_ADC0: U1.38 (GPIO26_ADC0); also elsewhere on the board
GPIO27_ADC1: U1.39 (GPIO27_ADC1); also elsewhere on the board
GPIO28_ADC2: U1.40 (GPIO28_ADC2); also elsewhere on the board
GPIO29_ADC3: U1.41 (GPIO29_ADC3); also elsewhere on the board
QSPI_SCLK: U1.52 (QSPI_SCLK); also elsewhere on the board
QSPI_SD0: U1.53 (QSPI_SD0); also elsewhere on the board
QSPI_SD1: U1.55 (QSPI_SD1); also elsewhere on the board
QSPI_SD2: U1.54 (QSPI_SD2); also elsewhere on the board
QSPI_SD3: U1.51 (QSPI_SD3); also elsewhere on the board
QSPI_SS: U1.56 (QSPI_SS); also elsewhere on the board
RUN: U1.26 (RUN); also elsewhere on the board
SWCLK: U1.24 (SWCLK); also elsewhere on the board
SWDIO: U1.25 (SWD); also elsewhere on the board
USB_DM: R13.1; also elsewhere on the board
USB_DP: R12.1; also elsewhere on the board
XIN: U1.20 (XIN); also elsewhere on the board
XOUT: U1.21 (XOUT); also elsewhere on the board

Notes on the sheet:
ADC current = ~150uA For best performance use external 3.0V shunt ref (e.g. LM4040) For lower offset (at expense of noise) connect VREF to 3V3 with lower resistance

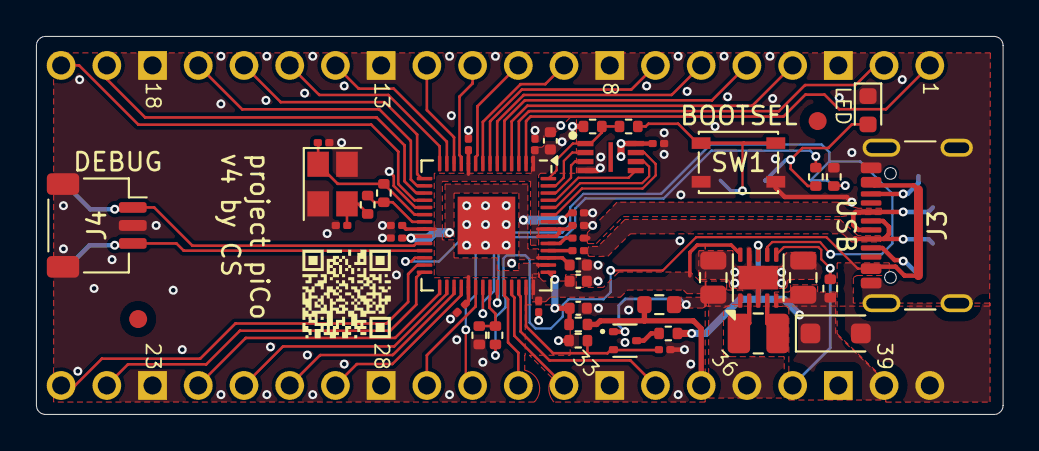
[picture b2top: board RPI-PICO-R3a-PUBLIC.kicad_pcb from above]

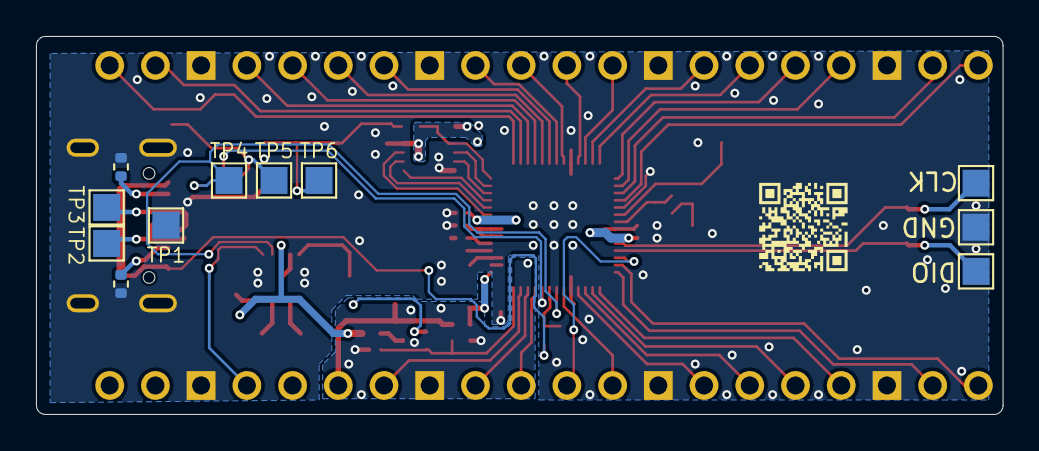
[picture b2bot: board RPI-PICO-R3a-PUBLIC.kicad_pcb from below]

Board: 2 copper layers, 53.7 x 21.0 mm, 59 parts (11 on the bottom side), 61 nets.

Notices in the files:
KiCad Projects/Pico C/RPI-PICO-R3a-PUBLIC - Official.kicad_pcb:
DESIGN FILES COPYRIGHT RASPBERRY PI 2020
